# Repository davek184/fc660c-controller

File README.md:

# FC660C Controller with USB-C

This revision was designed to maximize RGB underglow in the Norbauer Heavy-6 polycarb case.  To that end the reset button has been moved and is not accessible when installed in the case.  

RGB underglow lights can be added via a JST connector. Rooski15 has a great how to guide [here](https://www.keebtalk.com/t/adding-rgb-to-fc660c-with-hasu-controller/14484)

## Features
- Fully compatible with keymaps for Hasu's FC660C controller
- USB-C port (required small case modification)
- ESD protection circuit

## Bill of materials (BOM)
Please have a look at the manufacuring files!

_Ignore Rev1.0 it had problems with the LED connector.  Leaving in the Repo incase someone needs to refer back to them._

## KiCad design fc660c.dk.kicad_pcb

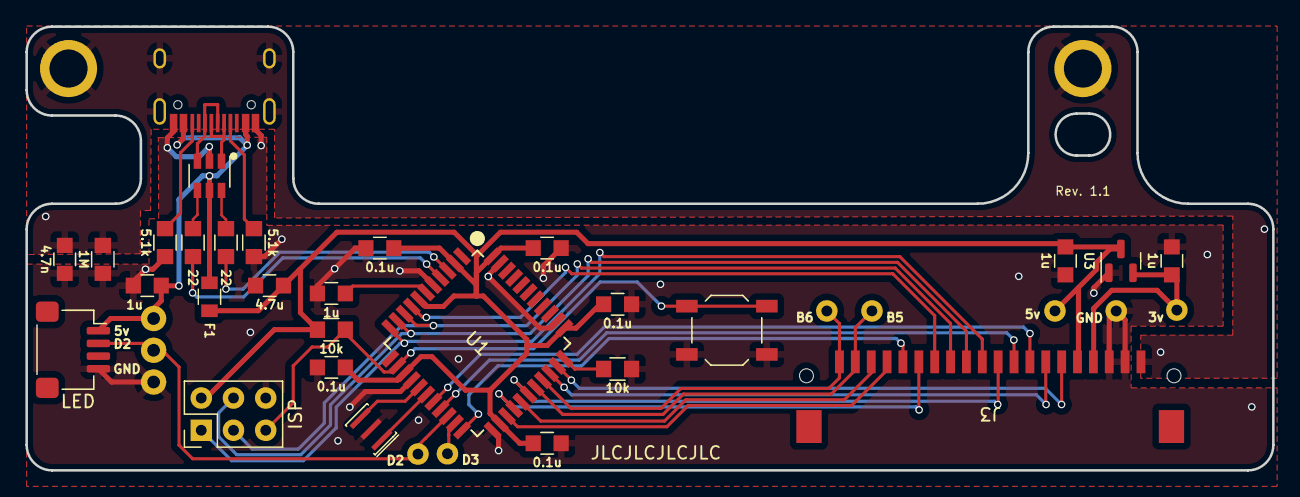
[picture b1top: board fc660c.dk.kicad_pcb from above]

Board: 2 copper layers, 98.2 x 35.0 mm, 31 parts (0 on the bottom side), 33 nets.

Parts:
C1, C2, C3, C4, C5: 0.1u; C_0805
C6: 4.7u; C_0805
C7, C9, C10, C11: 1u; C_0805
C8: 4.7n; C_0805
F1: Polyfuse_Small; F_0805
J1: HRO-TYPE-C-31-M-12
J2: ai03_ud; JST_SH_SM04B-SRSS-TB_1x04-1MP_P1.00mm_Horizontal
J2#2: ISP; isp_standard
J3: DF14-20P-1.25H
J4: Solder header; solder_header
R1, R2: 22; R_0805
R3, R4: 10k; R_0805
R5, R6: 5.1k; R_0805
R7: 1M; R_0805
S1, S2: SCREW; screw
SW1: SW_PUSH; SW_SPST_TL3342
U1: ATmega32U4; ATMEGA32U4
U2: USBLC6-2SC6
U3: XC6206P332MR; SOT-23
X1: 16mhz; Resonator_SMD_muRata_CSTNExxV-3Pin-p1.2

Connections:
+3V3: C10.1, J3.4, U3.2 (VO)
D+: R1.1, U2.4 (I/O2)
D-: R2.1, U2.6 (I/O1)
Earth: C8.1, J1.13 (SHIELD), J3.1, R7.2, S1.1, S2.1
GND: C1.2, C2.2, C3.2, C4.2, C5.2, C6.2, C7.2, C8.2, C9.1, C10.2, C11.2, J1.1 (GND), J1.12 (GND), J2.4, J2#2.6, J3.2, J3.3, J4.3, R4.2, R5.2, R6.2, R7.1, SW1.1, U1.5 (UGND), U1.15 (GND), U1.23 (GND), U1.35 (GND), U1.43 (GND), U2.2 (GND), U3.1 (GND), X1.3
MISO: J2#2.1, J3.11, U1.11 ((PDO/MISO/PCINT3)PB3)
MOSI: J2#2.4, J3.12, U1.10 ((PDI/MOSI/PCINT2)PB2)
unnamed: C7.1, U1.6 (UCAP)
unnamed: J1.4 (CC1), R5.1
unnamed: J1.5 (DN2), J1.7 (DN1), U2.1 (I/O1)
unnamed: J1.6 (DP1), J1.8 (DP2), U2.3 (I/O2)
unnamed: J1.10 (CC2), R6.1
unnamed: R1.2, U1.4 (D+)
unnamed: R2.2, U1.3 (D-)
unnamed: R4.1, U1.33 ((~HWB~)PE2)
unnamed: U1.16 (XTAL2), X1.2
unnamed: U1.17 (XTAL1), X1.1
P1: J3.20, U1.30 ((ADC13/OC1B/OC4B/PCINT13)PB6)
P2: J3.19, U1.29 ((ADC12/OC1A/~OC4B~/PCINT12)PB5)
P3: J3.18, U1.27 ((T0/OC4D/ADC10)PD7)
P4: J3.17, U1.25 ((ICP2/ADC8)PD4)
P5: J3.16, U1.22 ((XCK1/~CTS~)PD5)
P6: J3.15, U1.26 ((T1/~OC4D~/ADC9)PD6)
P7: J3.14, U1.8 ((SS/PCINT0)PB0)
P8: J2#2.3, J3.13, U1.9 ((SCLK/PCINT1)PB1)
P11: J3.10, U1.28 ((ADC11/PCINT4)PB4)
P12: J3.9, U1.19 ((SDA/INT1)PD1)
P13: J3.8, U1.18 ((OC0B/SCL/INT0)PD0)
P14: J3.7, U1.31 ((OC3A/~OC4A~)PC6)
P15: J3.6, U1.32 ((ICP3/CLK0/OC4A)PC7)
RST: J2#2.5, R3.2, SW1.2, U1.13 (RESET)
VBUS: C11.1, F1.2, J1.2 (VBUS), J1.11 (VBUS), J2.1, J4.1, U2.5 (VBUS)
VCC: C1.1, C2.1, C3.1, C4.1, C5.1, C6.1, C9.2, F1.1, J2#2.2, J3.5, R3.1, U1.2 (UVCC), U1.7 (VBUS), U1.14 (VCC), U1.24 (AVCC), U1.34 (VCC), U1.44 (AVCC), U3.3 (VI)

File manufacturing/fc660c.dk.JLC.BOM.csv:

Comment,Designator,Footprint,LCSC
100nf capacitor,"C1,C2,C3,C4,C5",805,C1711
4.7uf capacitor,C6,805,C1779
1uf capacitor,"C7,C9,C10,C11",805,C318694
4.7nF capacitor,C8,805,C21217
10k ohm resistor,"R3,R4",805,C163957
22 ohm resistor,"R1,R2",805,C168490
5.1k ohm resistor,"R5,R6",805,C164004
1M ohm resistor,R7,805,C163969
Microcontroller,U1,QFP-44,C44854
Diode ESD,U2,805,C7519
Resonator,X1,SMD,C341521
PTC Fuse,F1,SOT-23-6L,C261942
USB-C Connector,J1,SMD,C165948
Board to board connector,J3,TH,C506679
Tactile switch,SW1,SMD,C92584
JST Connector,J4,SMD,C160404
Linear Voltage Regulator 3.3V,U3,SMD,C347376

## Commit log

2022-05-14 Rev 1.1
2022-05-14 Adding old revision for archiving
    Don't use rev 1.0 there were problems with the LED data line and a few other minor problems.
2022-05-14 BOM Part Number Correction
2022-05-14 Sample Firmware
    Recommend compiling your own firmware with the appropriate number of LEDS.
2022-06-23 Adding JLC Manufacturing files
    June 2022 A set of PCBs with parts assembly has been made from these files
2022-11-11 Added photo
2022-12-16 Delete fc660c.dk.BOM.xls
    Removing as the other manufacturing files are generate from the PCB and more reliable
2022-12-16 Small Adjustments
    Corrected RGB Designator to be J4 (set ISP header J2 to not export to BOM/Place files)
2024-06-05 Firmware Updates
    A few people reported the Insert LED was always on using this controller. Precompiled VIAL firmware with a few different Insert LED functions and the latest from VIAL.
2024-06-05 Update readme.md
    Fixed URL references
2024-06-05 Firmware Updated 2
    Added Boot magic hold down esc when plugging in to enter boot load mode
